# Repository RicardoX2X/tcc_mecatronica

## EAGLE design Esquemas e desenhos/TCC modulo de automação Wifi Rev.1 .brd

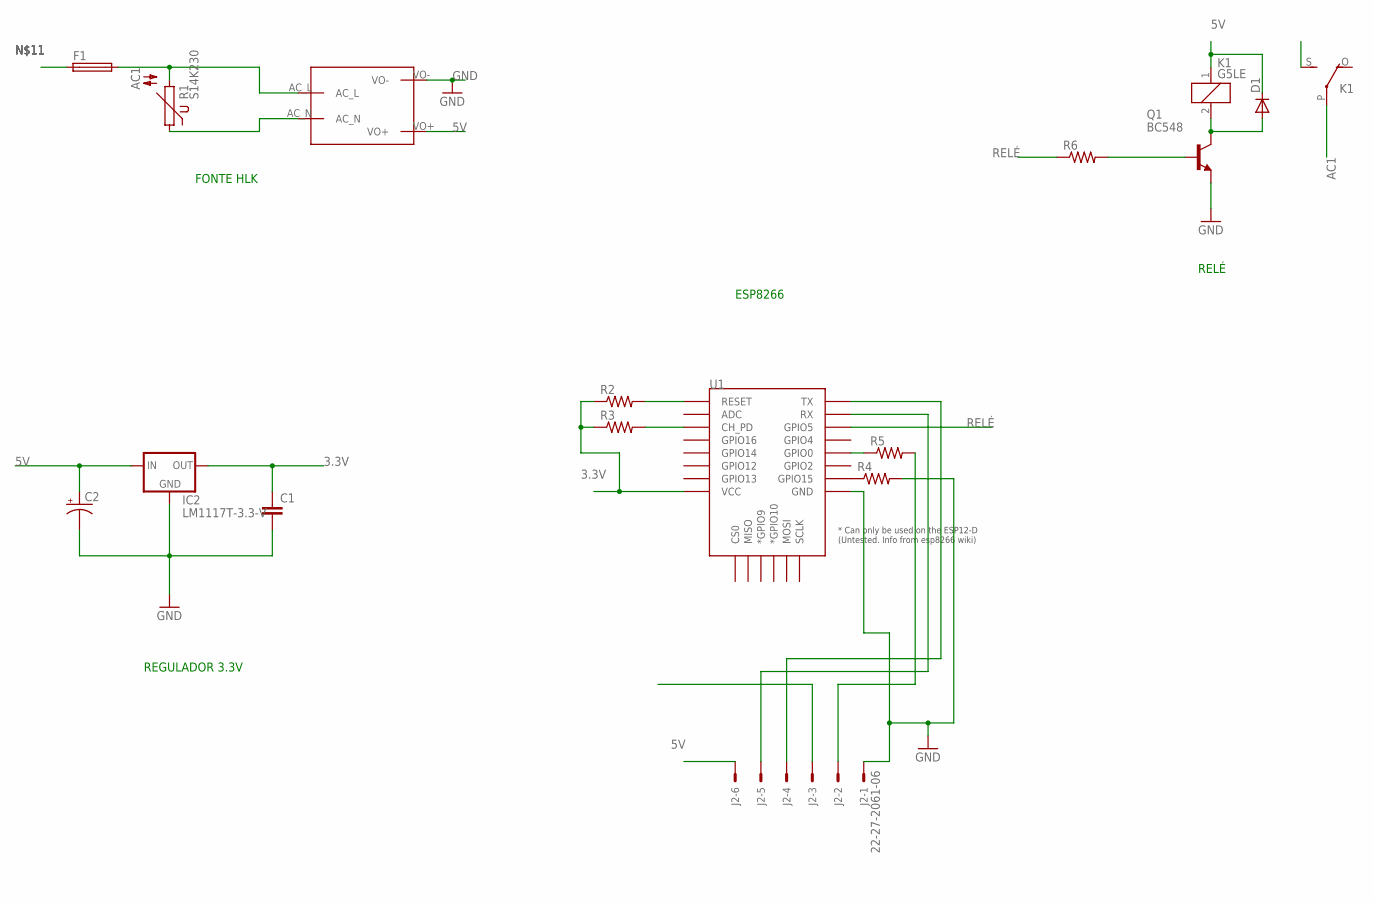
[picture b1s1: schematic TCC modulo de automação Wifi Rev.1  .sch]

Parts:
C1: C-EU050-025X075; C050-025X075
C2: CPOL-USE2-5; E2-5
D1: DIODE-SOD106A-R; SOD106A-R
F1: GSH15
IC2: LM1117T-3.3-V; TO220V
J2: 22-27-2061-06; 6410-06
K1: G5LE
Q1: BC548; TO92-EBC
R1: S14K230
R2, R3, R4, R5: R-US_M0805; M0805
R6: R-US_M1206; M1206
U1: ESP12ESMD; ESP12E-SMD
U$2: MAINS_CONVERTERS; HLK-PM01

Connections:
3.3V: C1.1, IC2.2 (OUT), R2.1, R3.1, U1.VCC
5V: C2.+, D1.C, IC2.3 (IN), J2.6, K1.1, U$2.VO+
787: R1.1, U$2.AC_N
AC1: F1.2, K1.P, R1.2, U$2.AC_L
GND: C1.2, C2.-, IC2.1 (GND), J2.1, Q1.E, R4.2, U1.GND, U$2.VO-
unnamed: R5.1, U1.GPIO0
unnamed: R4.1, U1.GPIO15
unnamed: Q1.B, R6.2
unnamed: D1.A, K1.2, Q1.C
unnamed: R2.2, U1.RESET
unnamed: J2.2, R5.2
unnamed: J2.4, U1.TXD0 (TX)
unnamed: J2.5, U1.RXD0 (RX)
unnamed: R3.2, U1.CH_PD
RELÉ: R6.1, U1.GPIO5

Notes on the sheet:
FONTE HLK
REGULADOR 3.3V
ESP8266
RELÉ

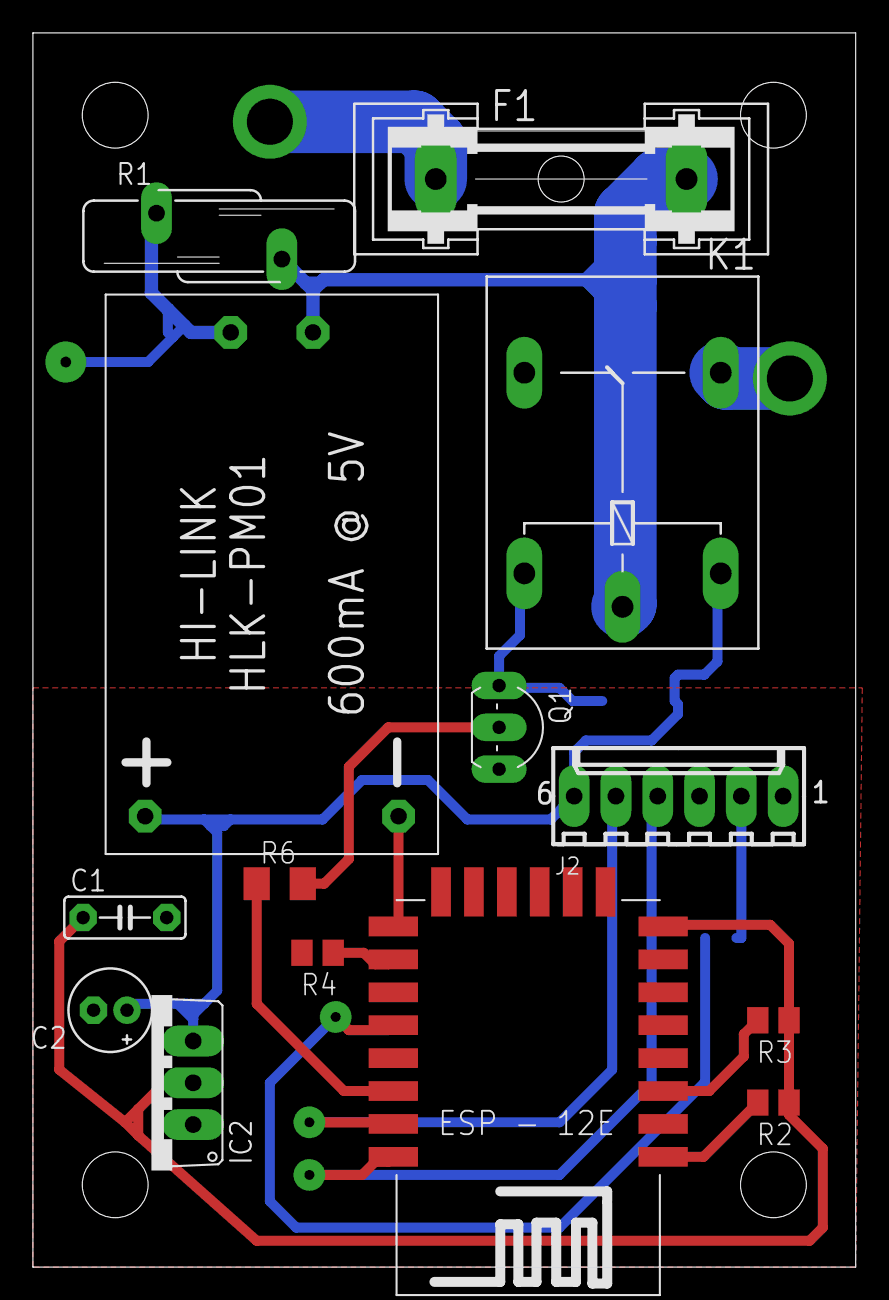
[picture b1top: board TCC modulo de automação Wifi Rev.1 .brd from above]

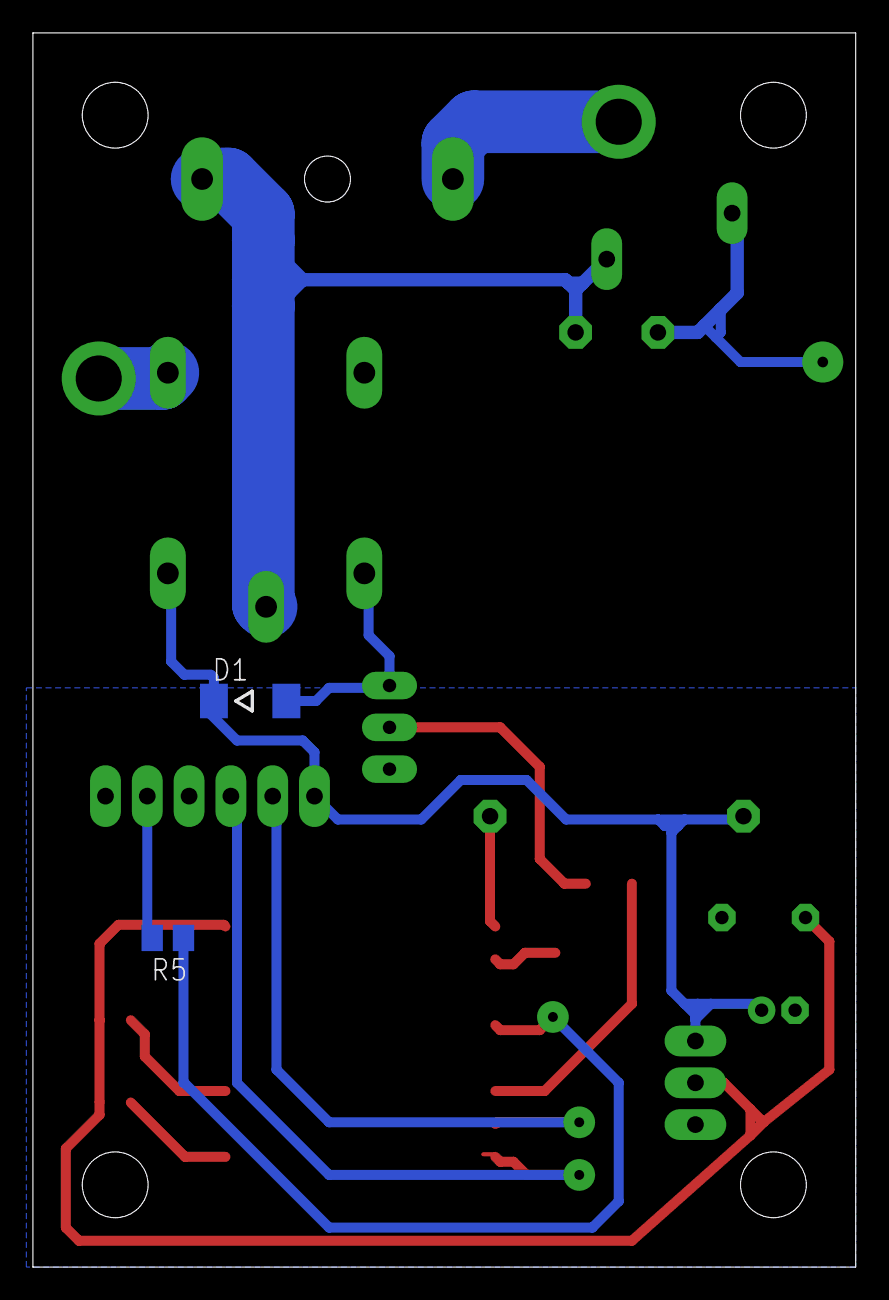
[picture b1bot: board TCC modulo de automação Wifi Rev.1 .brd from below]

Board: 2 copper layers, 50.0 x 75.0 mm, 16 parts (2 on the bottom side), 15 nets.

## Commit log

2023-04-04 the project was fineshed in 2017, but this is the initial commit
